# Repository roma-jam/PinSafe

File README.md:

# PinSafe

Here is a project to safety keeper pin codes. Based on security smartcard, cryptography and so on :)

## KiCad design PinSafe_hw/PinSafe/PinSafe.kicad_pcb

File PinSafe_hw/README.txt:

Here would be a hardware part for PinSafe project

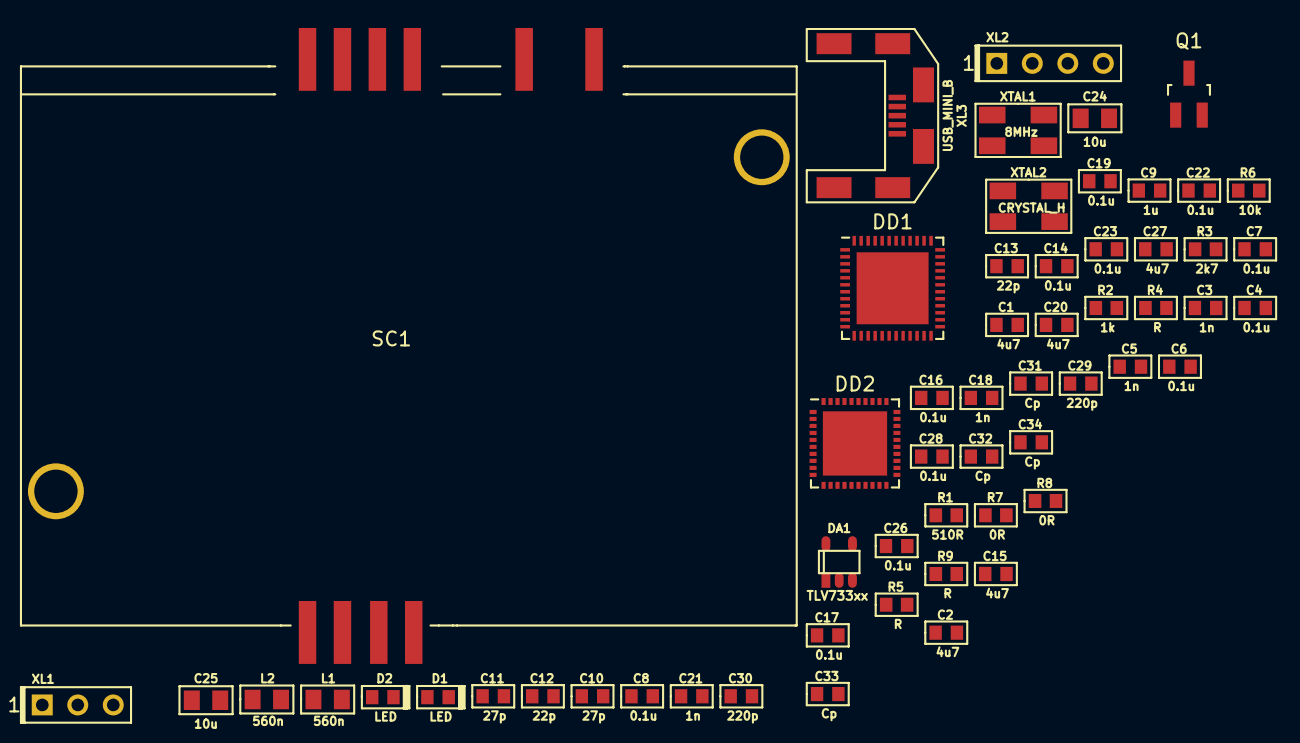
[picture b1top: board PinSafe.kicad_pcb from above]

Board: 2 copper layers, 57 parts (0 on the bottom side), 42 nets, no tracks yet.

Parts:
C1, C2, C15, C20, C27: 4u7; CAP_0603
C3, C5, C18, C21: 1n; CAP_0603
C4, C6, C7, C8, C14, C16, C17, C19, C22, C23, C26, C28: 0.1u; CAP_0603
C9: 1u; CAP_0603
C10, C11: 27p; CAP_0603
C12, C13: 22p; CAP_0603
C24, C25: 10u; CAP_0805
C29, C30: 220p; CAP_0603
C31, C32, C33, C34: Cp; CAP_0603
D1, D2: LED; LED_0603
DA1: TLV733xx; SOT23-5
DD1: STM32L151CCUx; QFN-48-1EP_7x7mm_Pitch0.5mm
DD2: PN532; QFN-40-1EP_6x6mm_Pitch0.5mm
L1, L2: 560n; IND_0805
Q1: IRLML6302; SOT-23_Handsoldering
R1: 510R; RES_0603
R2: 1k; RES_0603
R3: 2k7; RES_0603
R4, R5, R9: R; RES_0603
R6: 10k; RES_0603
R7, R8: 0R; RES_0603
SC1: IC_SC_CONNECTOR; IC_SMARTCARD_CONNECTOR_8-2
XL1: CONN_3; PLS-3
XL2: ST_SWD; PLS-4
XL3: USB_MINI_B; USBmicro_MOLEX_WM17142
XTAL1: 8MHz; 0503x4-4
XTAL2: CRYSTAL_H; 0503x4-4

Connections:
+3.3V: C1.1, C2.1, C3.1, C4.1, C5.1, C6.1, C7.1, C8.1, C9.1, C22.1, C26.1, C27.1, DA1.5, DD1.1, DD1.9, DD1.24, DD1.36, DD1.48, DD2.23, Q1.2, R6.1, XL2.1
+5V: C23.1, C24.1, C25.1, DA1.1, DA1.3, DD2.40, XL3.1
/ANT1: DD2.4, L1.2
/ANT2: DD2.6, L2.1
/DBG_RX: DD1.31, XL1.2
/DBG_TX: DD1.30, XL1.3
/LED_BLUE: D2.A, DD1.21
/LED_RED: D1.A, DD1.11
/PN_IRQ: DD1.19, DD2.25
/PN_MISO: DD1.40, DD2.29
/PN_MOSI: DD1.41, DD2.28
/PN_NSS: DD1.18, DD2.27
/PN_RESET: DD1.20, DD2.38
/PN_SCK: DD1.39, DD2.30
/PN_VDD: C14.1, C15.1, C17.1, C19.1, C20.1, C21.1, DD2.5, DD2.8, DD2.17, DD2.39
/RX_NET: C29.1, C31.2, L1.1, R3.1
/SC_CLK: DD1.13, SC1.3
/SC_IO: DD1.12, SC1.7
/SC_POWER: C28.1, Q1.3, SC1.1
/SC_RESET: DD1.16, SC1.2
/SC_STATE: DD1.14, SC1.9
/SC_VCC: DD1.17, Q1.1, R6.2
/SC_VPP: DD1.15, SC1.6
/SWCLK: DD1.37, XL2.2
/SWDIO: DD1.34, XL2.4
/USB_DM: DD1.32, XL3.2
/USB_DP: DD1.33, XL3.3
GND: C1.2, C2.2, C3.2, C4.2, C5.2, C6.2, C7.2, C8.2, C9.2, C10.2, C11.2, C12.2, C13.2, C14.2, C15.2, C16.2, C17.2, C19.2, C20.2, C21.2, C22.2, C23.2, C24.2, C25.2, C26.2, C27.2, C28.2, C29.2, C30.1, C33.2, C34.1, DA1.2, DD1.8, DD1.23, DD1.35, DD1.44, DD1.47, DD2.1, DD2.3, DD2.7, DD2.11, DD2.16, DD2.18, R4.2, R5.2, R8.2, SC1.GND, XL1.1, XL2.3, XL3.4, XL3.5, XL3.SHLD, XTAL1.H, XTAL2.H
unnamed: C10.1, R1.2, XTAL1.1
unnamed: C11.1, DD1.5, XTAL1.2
unnamed: C12.1, DD2.14, XTAL2.1
unnamed: C13.1, DD2.15, XTAL2.2
unnamed: C16.1, DD2.9, R2.2
unnamed: C18.1, R3.2
unnamed: C18.2, DD2.10, R2.1
unnamed: C30.2, C32.2, L2.2
unnamed: C31.1, C33.1, R7.2
unnamed: C32.1, C34.2, R9.2
unnamed: D1.C, R4.1
unnamed: D2.C, R5.1
unnamed: DD1.6, R1.1
unnamed: R7.1, R8.1, R9.1

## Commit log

2016-03-14 Add Applet Files.
2016-03-14 Add readme files.
2016-03-14 Add main logic functions - Pins, Storage, System.
    - Done System Info function.
2016-03-15 Version 0.5 Password logic added. - Add PASS class - Add HMAC class
2016-03-15 Update README files in project folders
2016-03-15 Add Visual Studio Project for PinSafe Project administration.
2016-03-16 Applet README.txt - commands description added
2016-03-16 Fix tabulation in README.txt
2016-03-20 Proceed scheme.
2016-03-20 Update HW project
2016-03-21 prepare to work with Storage. Should have cryptographic channel.
2016-03-21 hw: Add some pcb details
2016-03-21 Update gitignore list
2016-03-25 Add usb, leds, power transistor.
2016-04-01 Antenna pcb add
